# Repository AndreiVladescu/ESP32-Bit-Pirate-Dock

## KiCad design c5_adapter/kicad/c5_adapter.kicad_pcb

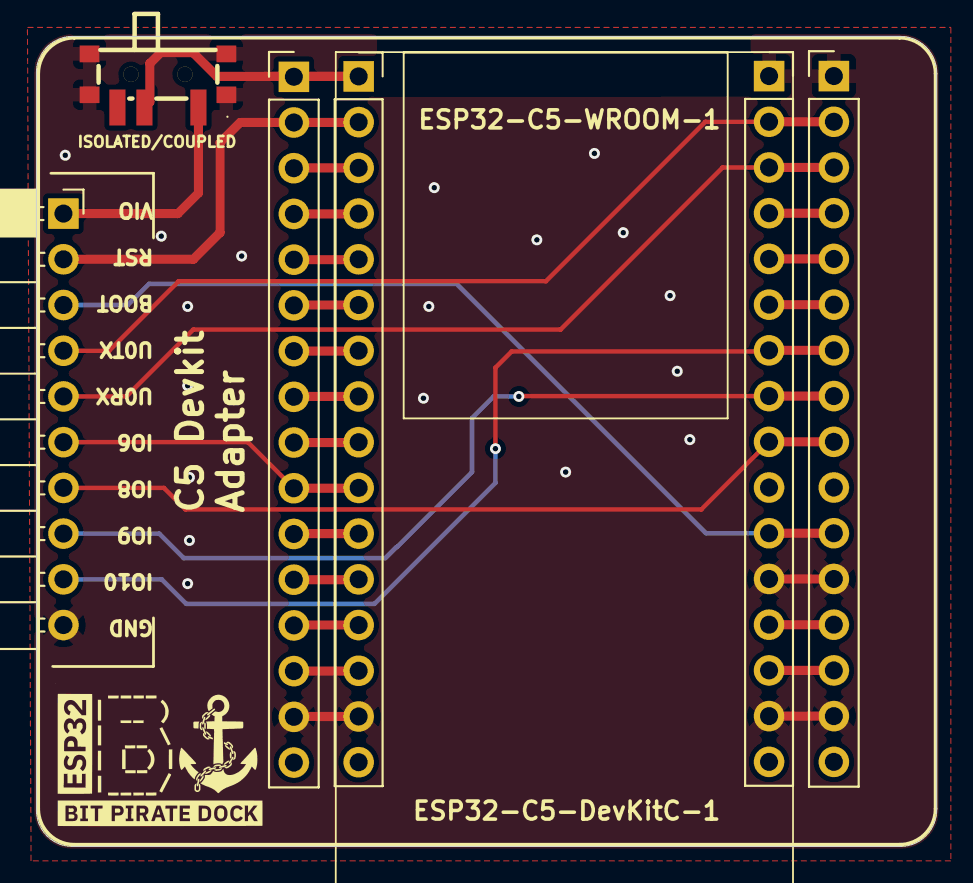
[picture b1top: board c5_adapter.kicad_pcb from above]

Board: 2 copper layers, 50.0 x 45.0 mm, 6 parts (0 on the bottom side), 27 nets.

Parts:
J1: Conn_01x10; PinSocket_1x10_P2.54mm_Horizontal
J3, J6: Conn_01x16; PinHeader_1x16_P2.54mm_Vertical
J4, J5: Conn_01x16; PinSocket_1x16_P2.54mm_Vertical
SW1: MK-12C02-G020; SW-SMD_MK-12C02-G020

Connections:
+3V3: J3.1, J4.1, SW1.2
+5V: J3.14, J4.14
BOOT: J1.3, J5.11, J6.11
GND: J1.10, J3.15, J4.15, J5.1, J5.12, J5.15, J6.1, J6.12, J6.15, SW1.4, SW1.5, SW1.6, SW1.7
IO6: J1.6, J3.10, J4.10
IO8: J1.7, J5.9, J6.9
IO9: J1.8, J5.8, J6.8
IO10: J1.9, J5.7, J6.7
unnamed: J3.3, J4.3
unnamed: J3.4, J4.4
unnamed: J3.5, J4.5
unnamed: J3.6, J4.6
unnamed: J3.7, J4.7
unnamed: J3.8, J4.8
unnamed: J3.9, J4.9
unnamed: J3.11, J4.11
unnamed: J3.12, J4.12
unnamed: J3.13, J4.13
unnamed: J5.4, J6.4
unnamed: J5.5, J6.5
unnamed: J5.6, J6.6
unnamed: J5.13, J6.13
unnamed: J5.14, J6.14
RST: J1.2, J3.2, J4.2
UART_RX: J1.5, J5.3, J6.3
UART_TX: J1.4, J5.2, J6.2
VIO_{DOCK}: J1.1, SW1.1

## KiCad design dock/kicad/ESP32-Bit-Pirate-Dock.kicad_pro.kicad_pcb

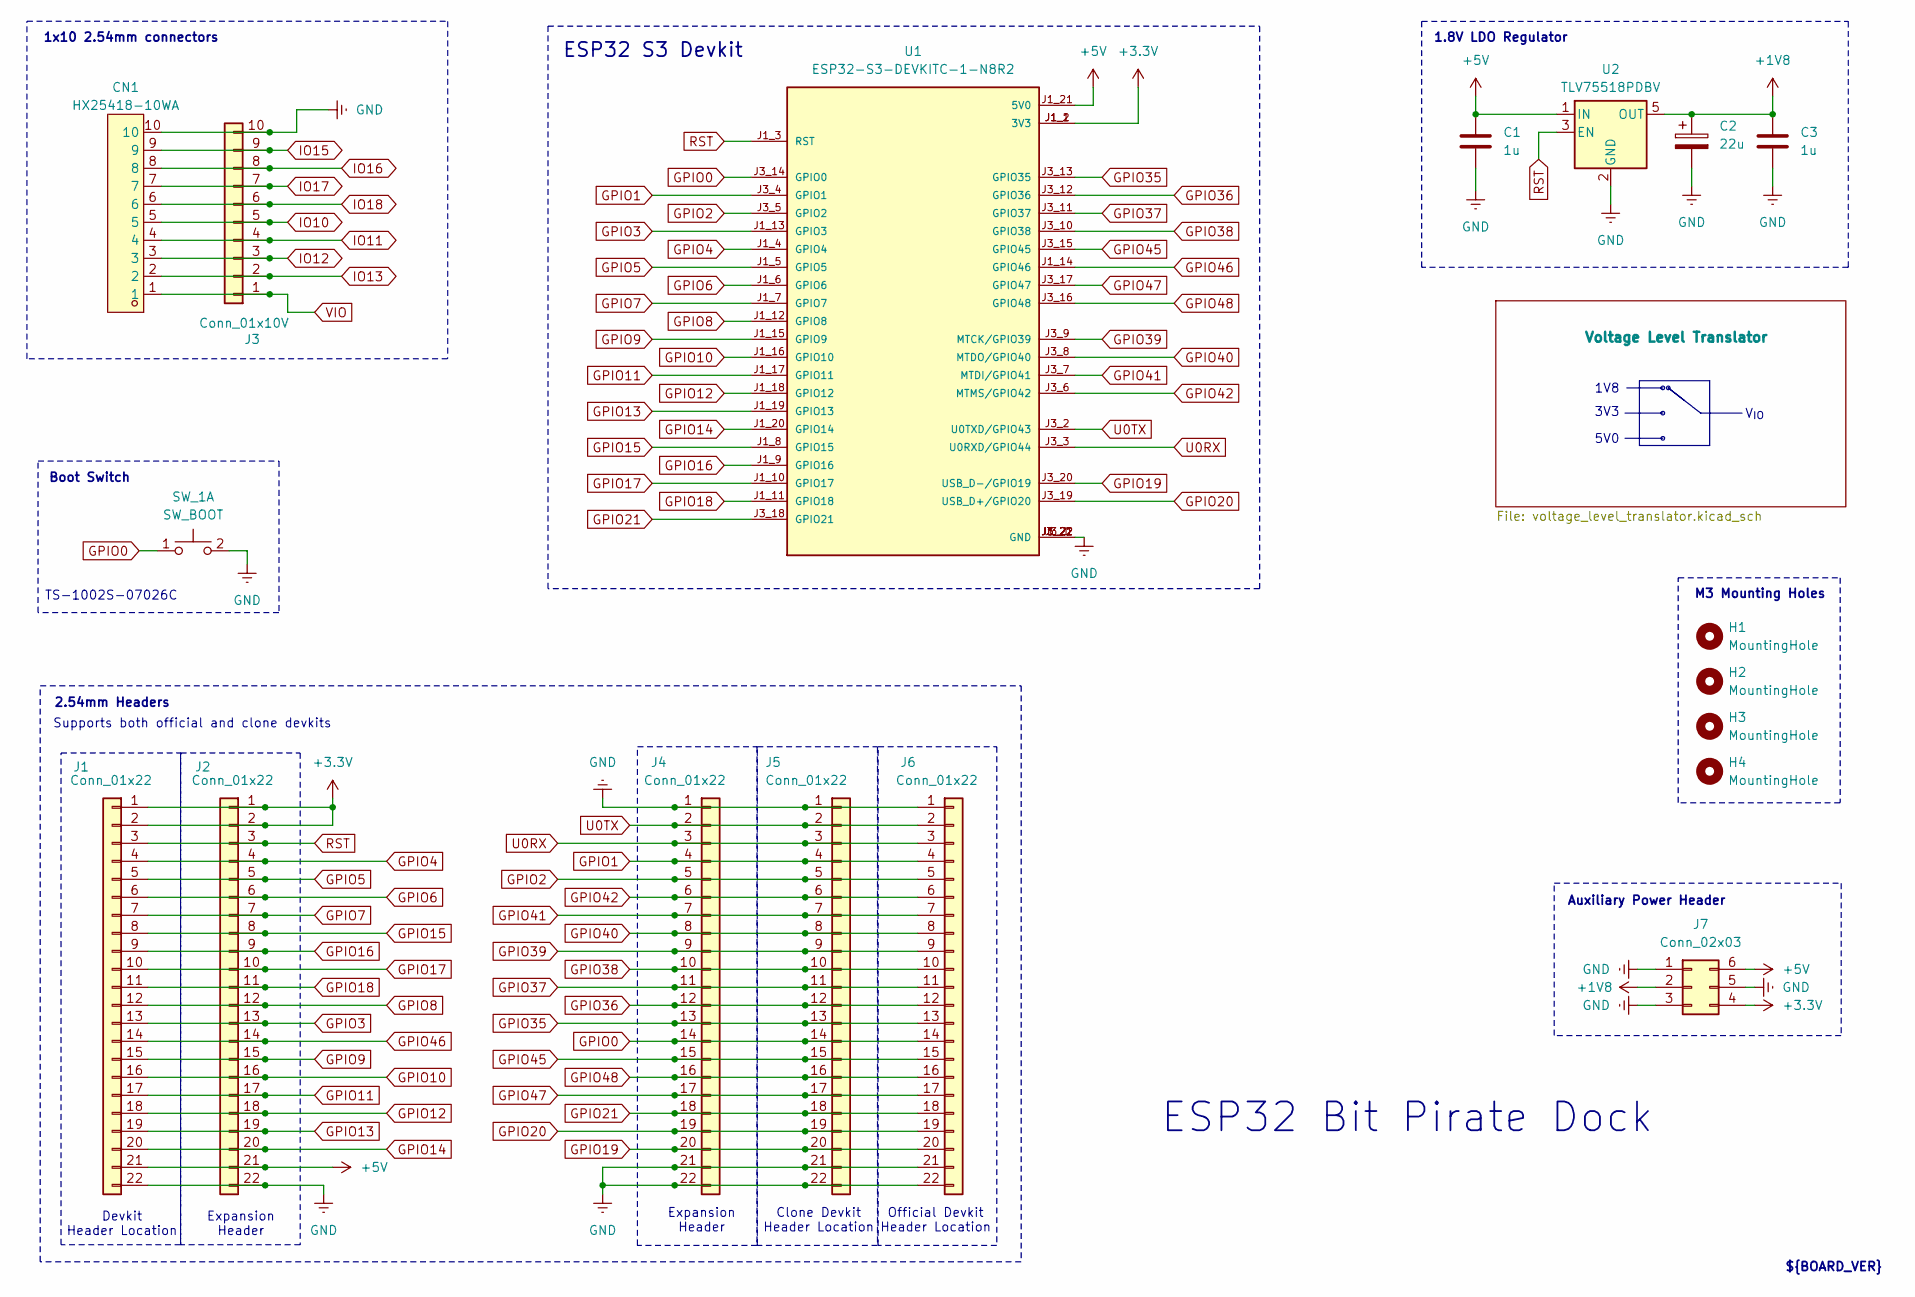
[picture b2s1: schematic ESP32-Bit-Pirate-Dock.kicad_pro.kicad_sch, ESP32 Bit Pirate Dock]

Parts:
C1, C3: 1u; C_0805_2012Metric
C2: 22u; CP_Elec_5x4.5
CN1: HX25418-10WA; CONN-TH_HX25418-10WA; LCSC Part C704586
H1, H2, H3, H4: MountingHole; MountingHole_3.2mm_M3_DIN965_Pad_TopBottom
J1, J5, J6: Conn_01x22; PinSocket_1x22_P2.54mm_Vertical
J2, J4: Conn_01x22; PinHeader_1x22_P2.54mm_Vertical
J3: Conn_01x10V; PinSocket_1x10_P2.54mm_Vertical
J7: Conn_02x03; PinHeader_2x03_P2.54mm_Vertical
SW_1: SW_BOOT; SW_SPST_PTS645Sx43SMTR92
U1: ESP32-S3-DEVKITC-1-N8R2; XCVR_ESP32-S3-DEVKITC-1-N8R2; PARTREV V1
U2: TLV75518PDBV; SOT-23-5

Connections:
+1V8: C2.1, C3.1, J7.2, U2.5 (OUT); also elsewhere on the board
+3.3V: J1.1, J1.2, J2.1, J2.2, J7.4, U1.J1_1 (3V3), U1.J1_2 (3V3); also elsewhere on the board
+5V: C1.1, J1.21, J2.21, J7.6, U1.J1_21 (5V0), U2.1 (IN); also elsewhere on the board
GND: C1.2, C2.2, C3.2, CN1.10, J1.22, J2.22, J3.10, J4.1, J4.21, J4.22, J5.1, J5.21, J5.22, J6.1, J6.21, J6.22, J7.1, J7.3, J7.5, SW_1.2 (D), U1.J1_22 (GND), U1.J3_1 (GND), U1.J3_21 (GND), U1.J3_22 (GND), U2.2 (GND); also elsewhere on the board
GPIO0: J4.14, J5.14, J6.14, SW_1.1 (C), U1.J3_14 (GPIO0)
GPIO1: J4.4, J5.4, J6.4, U1.J3_4 (GPIO1)
GPIO2: J4.5, J5.5, J6.5, U1.J3_5 (GPIO2)
GPIO3: J1.13, J2.13, U1.J1_13 (GPIO3)
GPIO4: J1.4, J2.4, U1.J1_4 (GPIO4)
GPIO5: J1.5, J2.5, U1.J1_5 (GPIO5)
GPIO6: J1.6, J2.6, U1.J1_6 (GPIO6)
GPIO7: J1.7, J2.7, U1.J1_7 (GPIO7)
GPIO8: J1.12, J2.12, U1.J1_12 (GPIO8)
GPIO9: J1.15, J2.15, U1.J1_15 (GPIO9)
GPIO10: J1.16, J2.16, U1.J1_16 (GPIO10); also elsewhere on the board
GPIO11: J1.17, J2.17, U1.J1_17 (GPIO11); also elsewhere on the board
GPIO12: J1.18, J2.18, U1.J1_18 (GPIO12); also elsewhere on the board
GPIO13: J1.19, J2.19, U1.J1_19 (GPIO13); also elsewhere on the board
GPIO14: J1.20, J2.20, U1.J1_20 (GPIO14)
GPIO15: J1.8, J2.8, U1.J1_8 (GPIO15); also elsewhere on the board
GPIO16: J1.9, J2.9, U1.J1_9 (GPIO16); also elsewhere on the board
GPIO17: J1.10, J2.10, U1.J1_10 (GPIO17); also elsewhere on the board
GPIO18: J1.11, J2.11, U1.J1_11 (GPIO18); also elsewhere on the board
GPIO19: J4.20, J5.20, J6.20, U1.J3_20 (USB_D-/GPIO19)
GPIO20: J4.19, J5.19, J6.19, U1.J3_19 (USB_D+/GPIO20)
GPIO21: J4.18, J5.18, J6.18, U1.J3_18 (GPIO21)
GPIO35: J4.13, J5.13, J6.13, U1.J3_13 (GPIO35)
GPIO36: J4.12, J5.12, J6.12, U1.J3_12 (GPIO36)
GPIO37: J4.11, J5.11, J6.11, U1.J3_11 (GPIO37)
GPIO38: J4.10, J5.10, J6.10, U1.J3_10 (GPIO38)
GPIO39: J4.9, J5.9, J6.9, U1.J3_9 (MTCK/GPIO39)
GPIO40: J4.8, J5.8, J6.8, U1.J3_8 (MTDO/GPIO40)
GPIO41: J4.7, J5.7, J6.7, U1.J3_7 (MTDI/GPIO41)
GPIO42: J4.6, J5.6, J6.6, U1.J3_6 (MTMS/GPIO42)
GPIO45: J4.15, J5.15, J6.15, U1.J3_15 (GPIO45)
GPIO46: J1.14, J2.14, U1.J1_14 (GPIO46)
GPIO47: J4.17, J5.17, J6.17, U1.J3_17 (GPIO47)
GPIO48: J4.16, J5.16, J6.16, U1.J3_16 (GPIO48)
IO10: CN1.5, J3.5; also elsewhere on the board
IO11: CN1.4, J3.4; also elsewhere on the board
IO12: CN1.3, J3.3; also elsewhere on the board
IO13: CN1.2, J3.2; also elsewhere on the board
IO15: CN1.9, J3.9; also elsewhere on the board
IO16: CN1.8, J3.8; also elsewhere on the board
IO17: CN1.7, J3.7; also elsewhere on the board
IO18: CN1.6, J3.6; also elsewhere on the board
RST: J1.3, J2.3, U1.J1_3 (RST), U2.3 (EN)
U0RX: J4.3, J5.3, J6.3, U1.J3_3 (U0RXD/GPIO44)
U0TX: J4.2, J5.2, J6.2, U1.J3_2 (U0TXD/GPIO43)
VIO: CN1.1, J3.1; also elsewhere on the board

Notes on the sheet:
Boot Switch
M3 Mounting Holes
${BOARD_VER}
1.8V LDO Regulator
TS-1002S-07026C
1x10 2.54mm connectors
Auxiliary Power Header
Clone Devkit Header Location
Expansion Header
Official Devkit Header Location
2.54mm Headers
Devkit Header Location
5V0
3V3
ESP32 S3 Devkit
1V8
V_{IO}
Supports both official and clone devkits
ESP32 Bit Pirate Dock

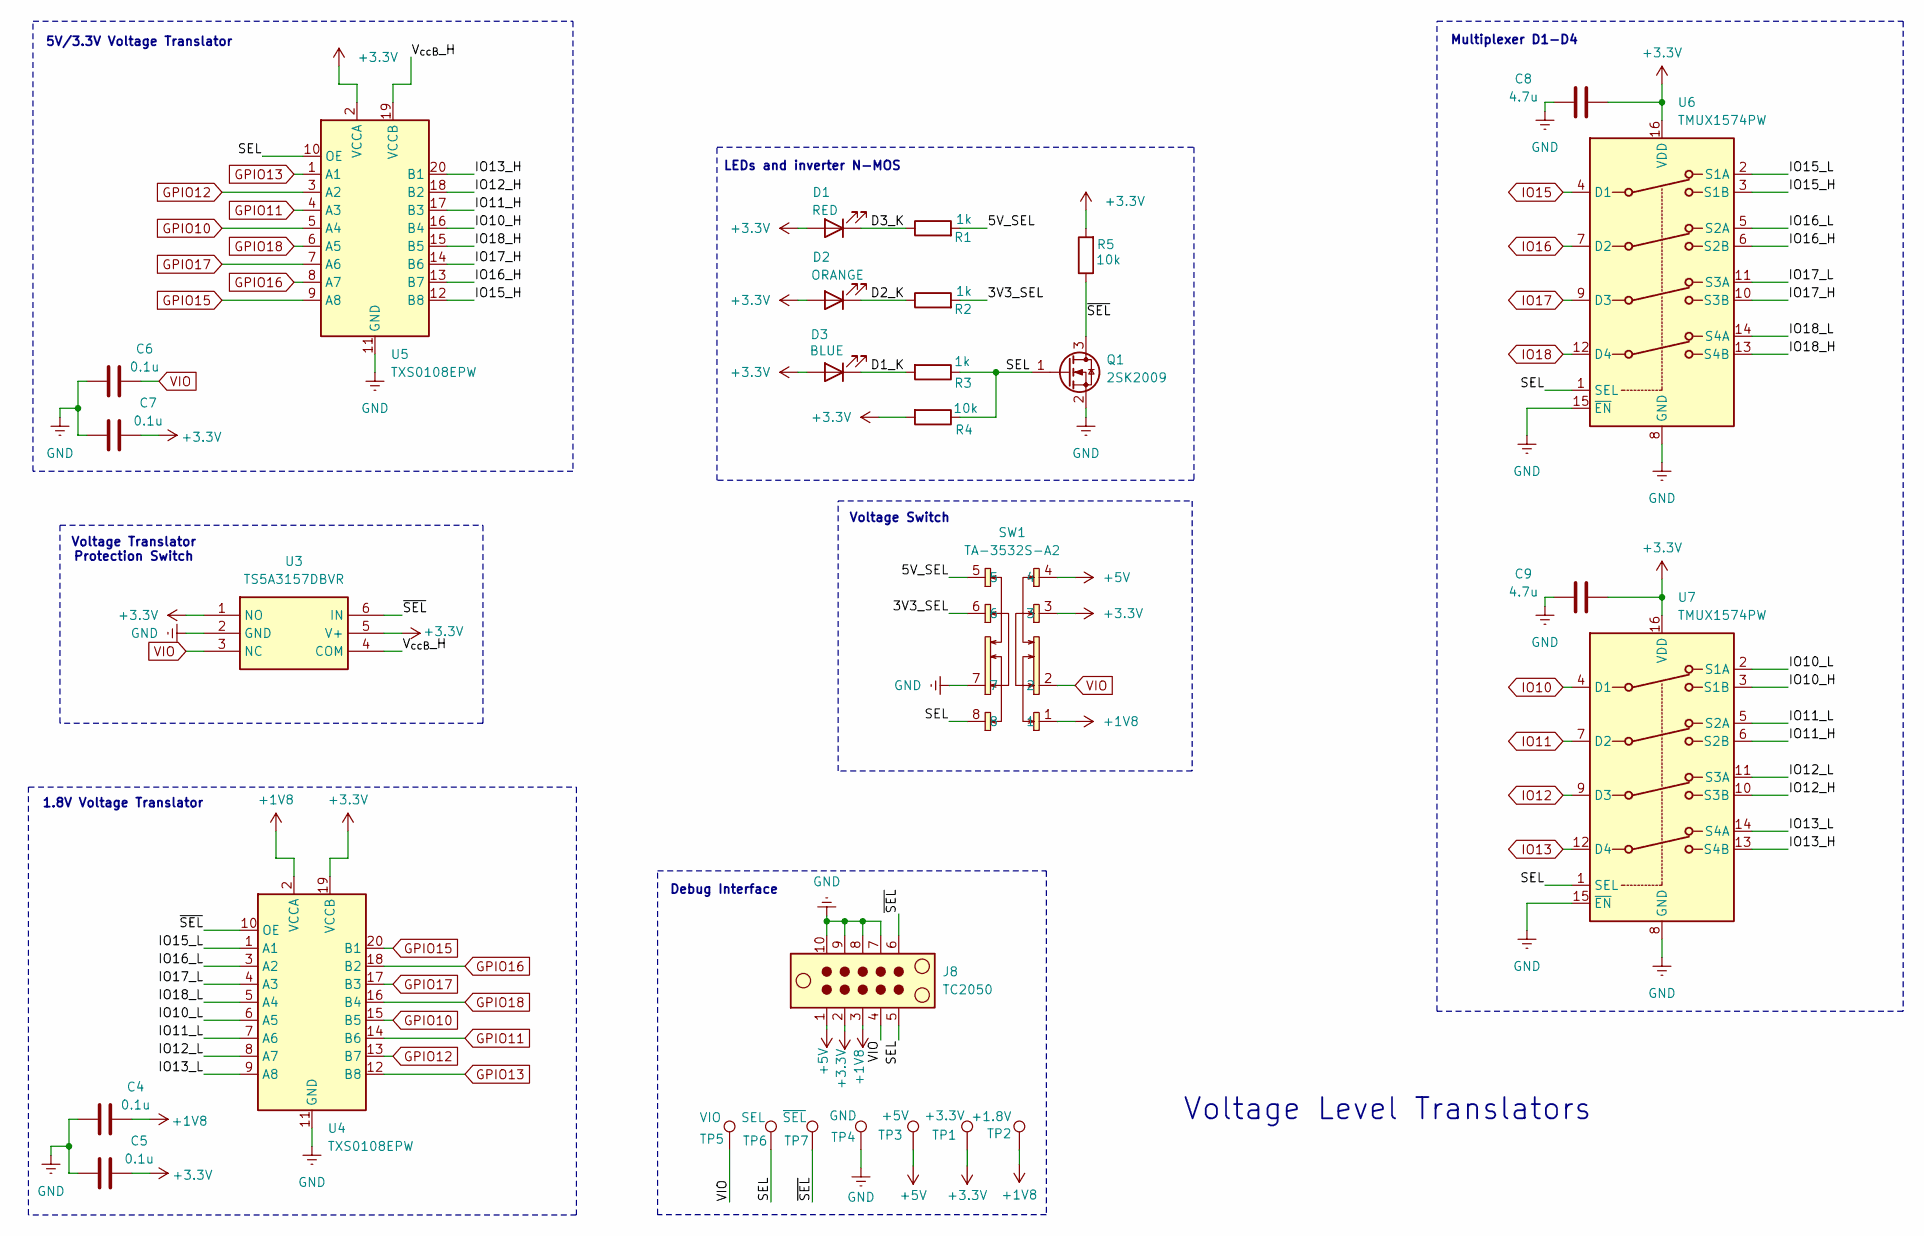
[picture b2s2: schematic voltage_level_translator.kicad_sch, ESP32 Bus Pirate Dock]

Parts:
C4, C5, C6, C7: 0.1u; C_0805_2012Metric
C8, C9: 4.7u; C_0805_2012Metric
D1: RED; LED_0805_2012Metric
D2: ORANGE; LED_0805_2012Metric
D3: BLUE; LED_0805_2012Metric
J8: TC2050; Tag-Connect_TC2050-IDC-NL_2x05_P1.27mm_Vertical_with_bottom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
Q1: 2SK2009; SOT-23
R1, R2, R3: 1k; R_0805_2012Metric
R4, R5: 10k; R_0805_2012Metric
SW1: TA-3532S-A2; SW-SMD_8P-L13.0-W3.5-P2.00; LCSC Part C514040
TP1: +3.3V; TestPoint_Pad_D1.0mm
TP2: +1.8V; TestPoint_Pad_D1.0mm
TP3: +5V; TestPoint_Pad_D1.0mm
TP4: GND; TestPoint_Pad_D1.0mm
TP5: VIO; TestPoint_Pad_D1.0mm
TP6: SEL; TestPoint_Pad_D1.0mm
TP7: ~{SEL}; TestPoint_Pad_D1.0mm
U3: TS5A3157DBVR; SOT95P280X145-6N; Mouser Part Number 595-TS5A3157DBVR
U4, U5: TXS0108EPW; Texas_PW0020A_TSSOP-20_4.4x6.5mm_P0.65mm
U6, U7: TMUX1574PW; TSSOP-16_4.4x5mm_P0.65mm

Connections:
+1V8: C4.1, J8.3, SW1.1, TP2.1, U4.2 (VCCA); also elsewhere on the board
+3.3V: C5.1, C7.1, C8.1, C9.1, D1.2 (A), D2.2 (A), D3.2 (A), J8.2, R4.2, R5.2, SW1.3, TP1.1, U3.1 (NO), U3.5 (V+), U4.19 (VCCB), U5.2 (VCCA), U6.16 (VDD), U7.16 (VDD); also elsewhere on the board
+5V: J8.1, SW1.4, TP3.1; also elsewhere on the board
/Voltage Level Translator/3V3_SEL: R2.2, SW1.6
/Voltage Level Translator/5V_SEL: R1.2, SW1.5
/Voltage Level Translator/D1_K: D3.1 (K), R3.2
/Voltage Level Translator/D2_K: D2.1 (K), R2.1
/Voltage Level Translator/D3_K: D1.1 (K), R1.1
/Voltage Level Translator/IO10_H: U5.16 (B4), U7.3 (S1B)
/Voltage Level Translator/IO10_L: U4.6 (A5), U7.2 (S1A)
/Voltage Level Translator/IO11_H: U5.17 (B3), U7.6 (S2B)
/Voltage Level Translator/IO11_L: U4.7 (A6), U7.5 (S2A)
/Voltage Level Translator/IO12_H: U5.18 (B2), U7.10 (S3B)
/Voltage Level Translator/IO12_L: U4.8 (A7), U7.11 (S3A)
/Voltage Level Translator/IO13_H: U5.20 (B1), U7.13 (S4B)
/Voltage Level Translator/IO13_L: U4.9 (A8), U7.14 (S4A)
/Voltage Level Translator/IO15_H: U5.12 (B8), U6.3 (S1B)
/Voltage Level Translator/IO15_L: U4.1 (A1), U6.2 (S1A)
/Voltage Level Translator/IO16_H: U5.13 (B7), U6.6 (S2B)
/Voltage Level Translator/IO16_L: U4.3 (A2), U6.5 (S2A)
/Voltage Level Translator/IO17_H: U5.14 (B6), U6.10 (S3B)
/Voltage Level Translator/IO17_L: U4.4 (A3), U6.11 (S3A)
/Voltage Level Translator/IO18_H: U5.15 (B5), U6.13 (S4B)
/Voltage Level Translator/IO18_L: U4.5 (A4), U6.14 (S4A)
/Voltage Level Translator/SEL: J8.5, Q1.1 (G), R3.1, R4.1, SW1.8, TP6.1, U5.10 (OE), U6.1 (SEL), U7.1 (SEL)
/Voltage Level Translator/V_{ccB}_H: U3.4 (COM), U5.19 (VCCB)
/Voltage Level Translator/~SEL: J8.6, Q1.3 (D), R5.1, TP7.1, U3.6 (IN), U4.10 (OE)
GND: C4.2, C5.2, C6.2, C7.2, C8.2, C9.2, J8.7, J8.8, J8.9, J8.10, Q1.2 (S), SW1.7, TP4.1, U3.2 (GND), U4.11 (GND), U5.11 (GND), U6.8 (GND), U6.15 (~EN), U7.8 (GND), U7.15 (~EN); also elsewhere on the board
GPIO10: U4.15 (B5), U5.5 (A4); also elsewhere on the board
GPIO11: U4.14 (B6), U5.4 (A3); also elsewhere on the board
GPIO12: U4.13 (B7), U5.3 (A2); also elsewhere on the board
GPIO13: U4.12 (B8), U5.1 (A1); also elsewhere on the board
GPIO15: U4.20 (B1), U5.9 (A8); also elsewhere on the board
GPIO16: U4.18 (B2), U5.8 (A7); also elsewhere on the board
GPIO17: U4.17 (B3), U5.7 (A6); also elsewhere on the board
GPIO18: U4.16 (B4), U5.6 (A5); also elsewhere on the board
IO10: U7.4 (D1); also elsewhere on the board
IO11: U7.7 (D2); also elsewhere on the board
IO12: U7.9 (D3); also elsewhere on the board
IO13: U7.12 (D4); also elsewhere on the board
IO15: U6.4 (D1); also elsewhere on the board
IO16: U6.7 (D2); also elsewhere on the board
IO17: U6.9 (D3); also elsewhere on the board
IO18: U6.12 (D4); also elsewhere on the board
VIO: C6.1, J8.4, SW1.2, TP5.1, U3.3 (NC); also elsewhere on the board

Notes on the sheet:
Voltage Level Translators
5V/3.3V Voltage Translator
Voltage Switch
LEDs and inverter N-MOS
Debug Interface
Voltage Translator Protection Switch
Multiplexer D1-D4
1.8V Voltage Translator

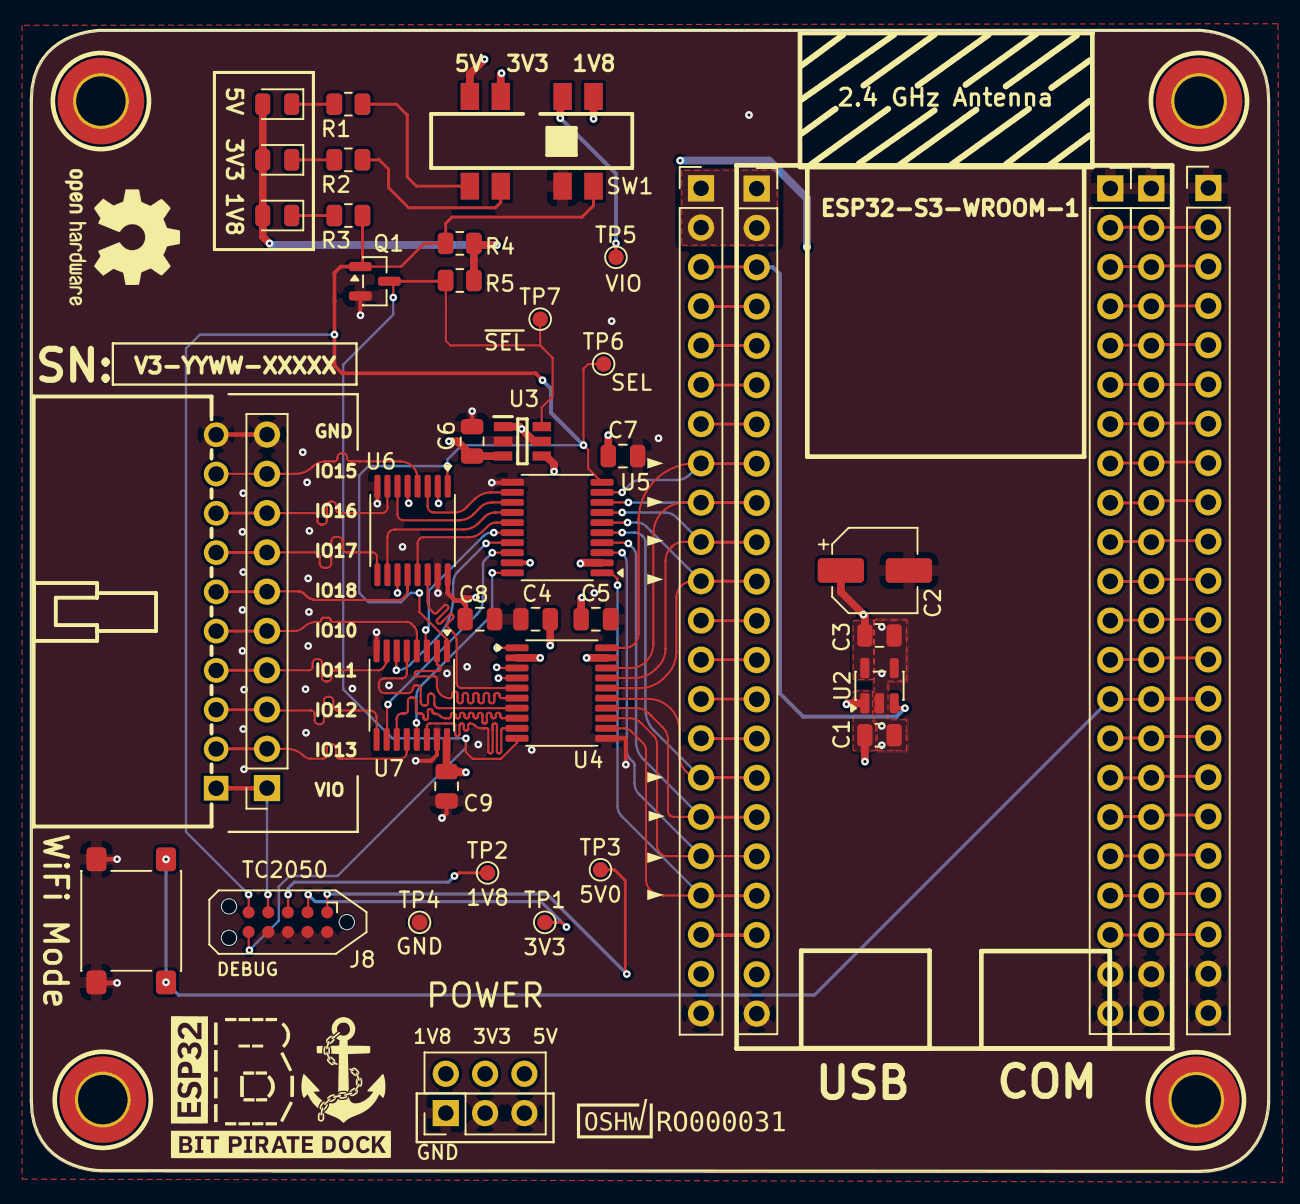
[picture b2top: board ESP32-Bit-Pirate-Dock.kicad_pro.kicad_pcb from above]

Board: 4 copper layers, 80.0 x 73.8 mm, 46 parts (0 on the bottom side), 74 nets.
